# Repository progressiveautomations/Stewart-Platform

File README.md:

# Stewart Platform

## Table of Contents
[Quick Start Guide](#qsg)

[Wiring the Electronics](#wiring)

[Mechanical Assembly](#mech)

[Troubleshooting](#ts)

<a name="qsg"/>

# Quick Start Guide
1. Ensure that power to the platform is turned off, the USB cable from the platform is unplugged from the computer, and all GUI instances are closed.
2. (if Leap Motion is to be used) Ensure that the Leap Motion service and software is started, and the controller is plugged into the computer.
3. Turn on the power to the platform, and plug the USB cable from the platform into the computer.
4. Launch the GUI; in the 'Options' menu, click "Select COM Port".
5. Find the COM port corresponding to the Arduino Due (should show up in the Device Description on the left hand side, as shown), and change the baud rate to 115200.
6. Click connect, and the platform should immediately begin its calibration routine by moving all actuators to full extension, and retracting to minimum position. DO NOT SEND ANY COMMANDS TO THE PLATFORM DURING THIS PHASE!
7. Check the beginning of the log to ensure calibration has succeeded.
8. Manually control the actuators by moving the sliders and/or entering values into the corresponding textbox. To enable Leap Motion, ensure its status is "Connected", and tick the "Enable Leap Motion" checkbox above the sliders.

# Assembly Instructions

<a name="wiring"/>

## Wiring the Electronics

Before assembly, ensure that all the wires are adequately connected within the enclosure, including the power supply wires, the actuator power wires, the actuator signal wires, and the Arduino Due wires. Detail in [how the components are wired together](electronics/electronics_layout.pdf) and individual schematics are located in the `electronics` folder.

To ensure the code under `arduino/platform` is compatible with the wiring of the Arduino Due, the headers on the PCB should be connected to the respective pins in the table below. This assumes actuators 1 through 3 are connected to Multimoto 1 (to blocks M3, M2, and M1 respectively) and actuators 4 through 6 similarly to Multimoto 2. Note the actuator indexing for the PCBs differs from that in software.
- The indexing on the PCBs are ordered by the motor blocks on the Multimoto boards. Indices 1 through 4 correspond to M1 through M4 on Multimoto 1, and the same for indices 5 though 8 with Multimoto 2.
- The indexing in software is ordered by how the signal wires interface with the PCB terminal blocks. This should match the order (left to right) in which they are connected to the enclosure ports.

The UTIL pin headers (RESET, +3.3V, +5V, GND, GND, Vin) are connected to the identically-named Arduino pins and are omitted from this list. The exact pin numbering can be updated in software at `arduino/platform/pin_layout.h` if the wiring configuration needs to be modified.

| Header   | Pin |
|----------|----:|
| POT_1    |  A6 |
| POT_2    |  A7 |
| POT_3    |  A8 |
| POT_4    |  A9 |
| POT_5    | A10 |
| POT_6    | A11 |
| DIR_1    |  41 |
| DIR_2    |  39 |
| DIR_3    |  37 |
| DIR_5    |  35 |
| DIR_6    |  33 |
| DIR_7    |  31 |
| PWM_1    |  13 |
| PWM_2    |  12 |
| PWM_3    |  11 |
| PWM_5    |  10 |
| PWM_6    |   9 |
| PWM_7    |   8 |
| ENABLE_1 |  24 |
| ENABLE_2 |  25 |

<a name="mech"/>

## Mechanical Assembly

Attach the 3 platform legs to the 3 corners of the base plate (Note: the base plate is larger than the top plate, and has 4 slots cut into it.), such that the 6 metal flanges are facing upwards. This is done using the ¾” long, ⅜”-16 threaded bolts, with one washer.

Next, position the enclosure underneath the base, so that the enclosure posts align with the slots in the base plate, with the power and USB connectors facing out as shown.

Attach the enclosure to the base place using 4 1” long,  ¼”-20 threaded bolts, with a washer for each. Ensure the bolts are aligned in the slots such that the corners of the enclosure do not extend beyond the edge of the base plates, like shown.

Attach the actuators as shown in the following picture. Close-up views of the joints are provided. Use 2 washers (one on each side), a lock-washer, and a ¼”-28 nut.

To avoid problems, ensure that the actuator gearboxes are facing upwards as shown in the picture.

Once the platform is assembled, attach the maze to the top plate by aligning the 3 corner holes on each, and secure it with 3 1¼” long, ⅜”-16 threaded bolts, with one washer on each, and a nut.

Connect all the actuator connectors to the appropriate receptacles on the enclosure, by routing the cables around and under the base plate. These can be bundled to be neat and out-of-view.

Finally, connect the power and USB cables to the front of the enclosure, and connect the other end of the USB cable. The platform is now assembled!

<a name="ts"/>

# Troubleshooting

Nothing is moving? Check all power connectors.

Arduino not seen by computer? Check USB cable connection, and ensure the device shows up in Device Manager.

Noisy actuator readings? Adjust the PWM feedback or the filtering capacitances on the Arduino PCB.

## PCB design
The PCBs were designed using [KiCAD v4.0.7](http://kicad.org/).

Each board has its design files under the `electronics` folder, along with Gerber files (under `electronics/gerber`) for the case of reproduction. The individual netlists can be found in the `.sch` files.

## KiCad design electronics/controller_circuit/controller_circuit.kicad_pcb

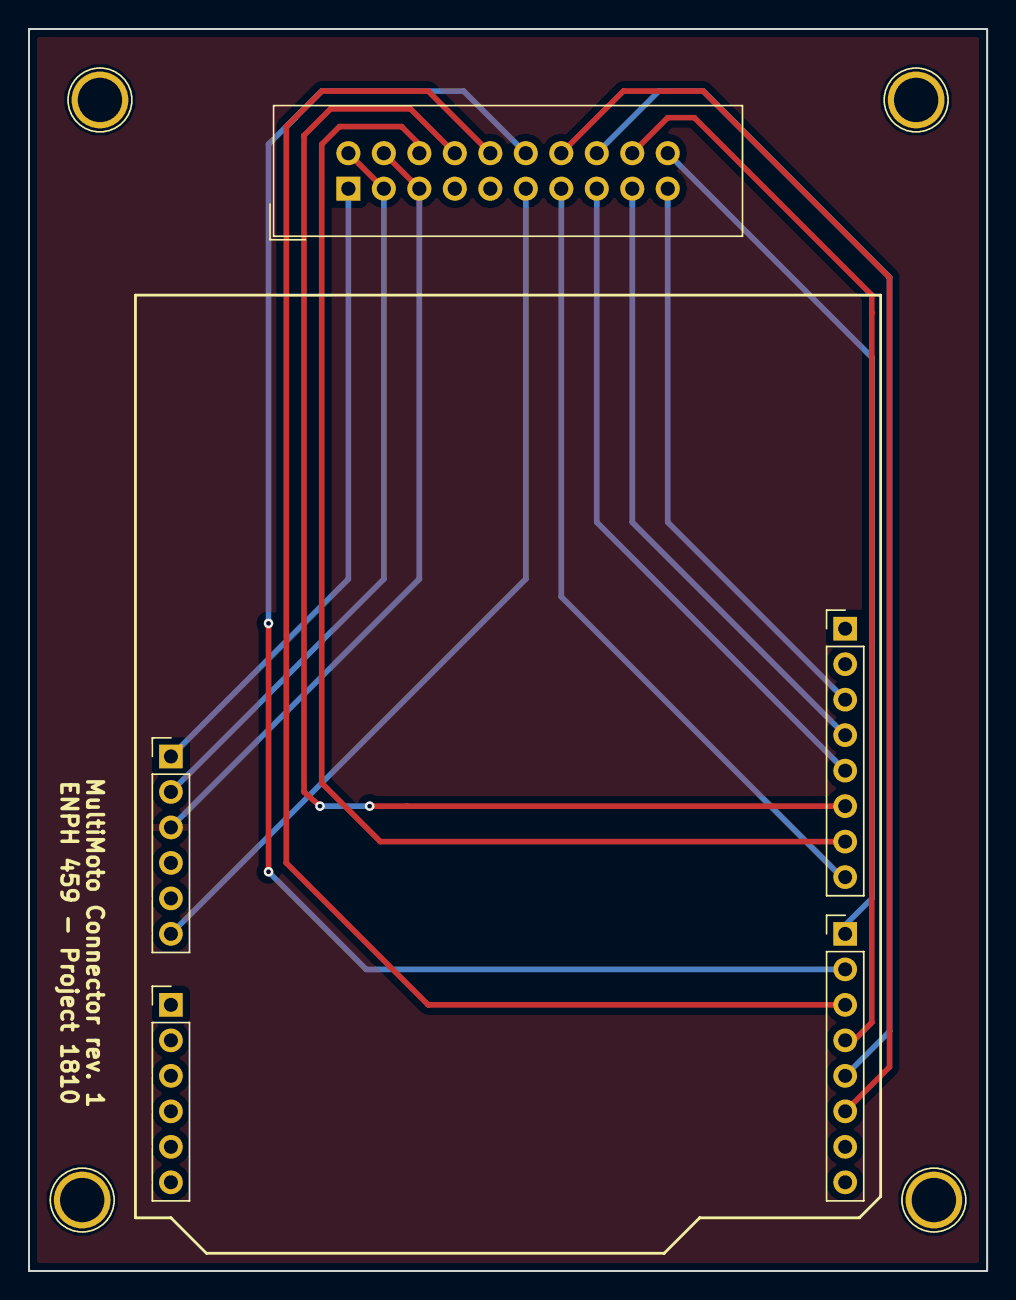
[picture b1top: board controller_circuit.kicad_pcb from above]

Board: 2 copper layers, 68.6 x 88.9 mm, 5 parts (0 on the bottom side), 17 nets.

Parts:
J1: HEADER_10x2; IDC-Header_2x10_Pitch2.54mm_Straight
J2, J3: HEADER_6; Socket_Strip_Straight_1x06_Pitch2.54mm
J4, J5: HEADER_8; Socket_Strip_Straight_1x08_Pitch2.54mm

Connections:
+3.3V: J1.2, J1.3, J2.2
+5V: J1.4, J1.5, J2.3
DIR_1: J1.14, J5.6
DIR_2: J1.16, J5.5
DIR_3: J1.18, J5.4
DIR_4: J1.20, J5.1
GND: J1.7, J1.9, J2.4, J2.5
MISO: J1.17, J4.4
MOSI: J1.15, J4.5
PWM_1: J1.6, J4.7
PWM_2: J1.8, J4.6
PWM_3: J1.10, J5.3
PWM_4: J1.12, J5.2
RESET: J1.1, J2.1
SCLK: J1.19, J4.3
Vin: J1.11, J2.6
~ENABLE~: J1.13, J4.8

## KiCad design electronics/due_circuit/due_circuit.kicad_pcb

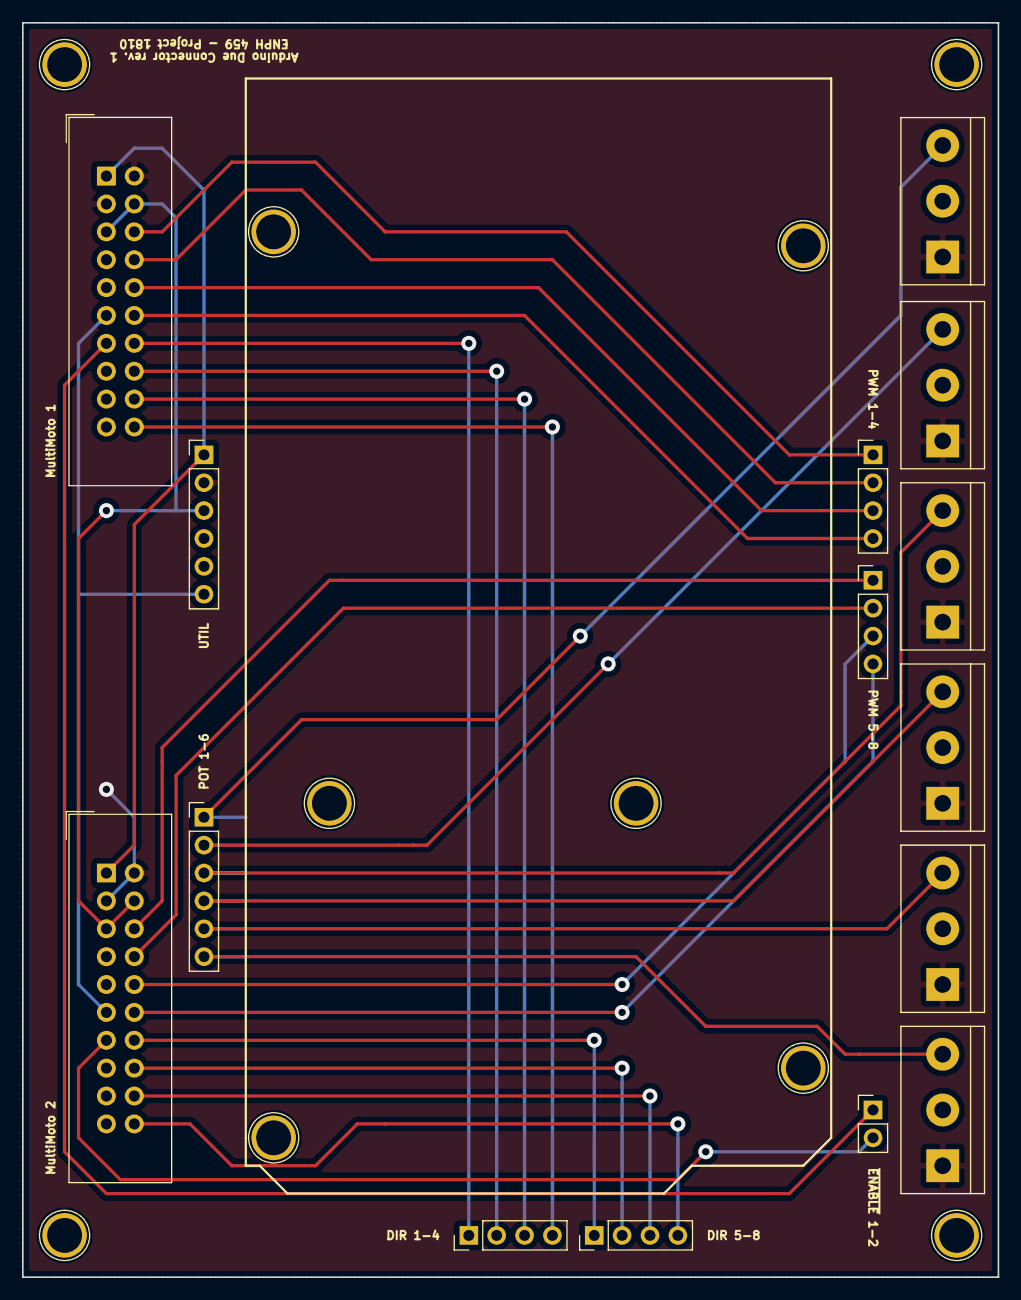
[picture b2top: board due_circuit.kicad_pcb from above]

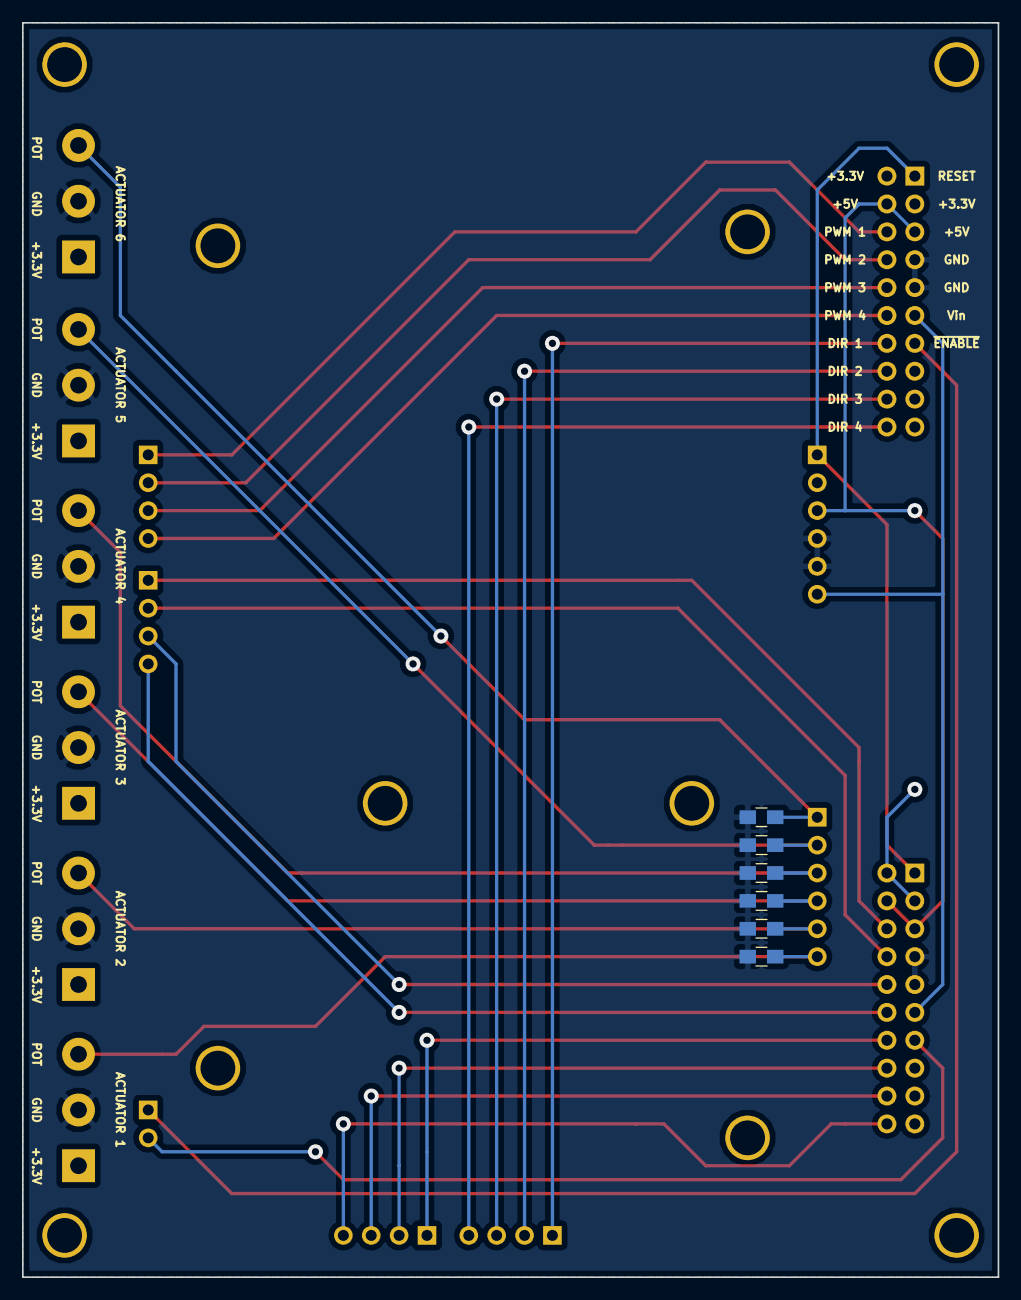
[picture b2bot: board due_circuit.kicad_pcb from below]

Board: 2 copper layers, 88.9 x 114.3 mm, 20 parts (6 on the bottom side), 27 nets.

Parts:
ACTUATOR_1, ACTUATOR_2, ACTUATOR_3, ACTUATOR_4, ACTUATOR_5, ACTUATOR_6: HEADER_3; TerminalBlock_bornier-3_P5.08mm
C1, C2, C3, C4, C5, C6: 10nF; C_0805_HandSoldering
DIR_1-4, DIR_5-8: HEADER_4; Pin_Header_Straight_1x04_Pitch2.54mm
MULTIMOTO_1, MULTIMOTO_2: HEADER_10x2; IDC-Header_2x10_Pitch2.54mm_Straight
POT_OUT_1: HEADER_6; Pin_Header_Straight_1x06_Pitch2.54mm
PWM_1-4, PWM_5-8: HEADER_4; Pin_Header_Straight_1x04_Pitch2.54mm
UTIL_1: HEADER_6; Pin_Header_Straight_1x06_Pitch2.54mm

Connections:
+3.3V: ACTUATOR_1.1, ACTUATOR_2.1, ACTUATOR_3.1, ACTUATOR_4.1, ACTUATOR_5.1, ACTUATOR_6.1, MULTIMOTO_1.2, MULTIMOTO_1.3, MULTIMOTO_2.2, MULTIMOTO_2.3, UTIL_1.2
+5V: MULTIMOTO_1.4, MULTIMOTO_1.5, MULTIMOTO_2.4, MULTIMOTO_2.5, UTIL_1.3
DIR_1: DIR_1-4.1, MULTIMOTO_1.14
DIR_2: DIR_1-4.2, MULTIMOTO_1.16
DIR_3: DIR_1-4.3, MULTIMOTO_1.18
DIR_4: DIR_1-4.4, MULTIMOTO_1.20
DIR_5: DIR_5-8.1, MULTIMOTO_2.14
DIR_6: DIR_5-8.2, MULTIMOTO_2.16
DIR_7: DIR_5-8.3, MULTIMOTO_2.18
DIR_8: DIR_5-8.4, MULTIMOTO_2.20
GND: ACTUATOR_1.2, ACTUATOR_2.2, ACTUATOR_3.2, ACTUATOR_4.2, ACTUATOR_5.2, ACTUATOR_6.2, C1.2, C2.2, C3.2, C4.2, C5.2, C6.2, MULTIMOTO_1.7, MULTIMOTO_1.9, MULTIMOTO_2.7, MULTIMOTO_2.9, UTIL_1.4, UTIL_1.5
POT_1: ACTUATOR_1.3, C1.1, POT_OUT_1.6
POT_2: ACTUATOR_2.3, C2.1, POT_OUT_1.5
POT_3: ACTUATOR_3.3, C3.1, POT_OUT_1.4
POT_4: ACTUATOR_4.3, C4.1, POT_OUT_1.3
POT_5: ACTUATOR_5.3, C5.1, POT_OUT_1.2
POT_6: ACTUATOR_6.3, C6.1, POT_OUT_1.1
PWM_1: MULTIMOTO_1.6, PWM_1-4.1
PWM_2: MULTIMOTO_1.8, PWM_1-4.2
PWM_3: MULTIMOTO_1.10, PWM_1-4.3
PWM_4: MULTIMOTO_1.12, PWM_1-4.4
PWM_5: MULTIMOTO_2.6, PWM_5-8.1
PWM_6: MULTIMOTO_2.8, PWM_5-8.2
PWM_7: MULTIMOTO_2.10, PWM_5-8.3
PWM_8: MULTIMOTO_2.12, PWM_5-8.4
RESET: MULTIMOTO_1.1, MULTIMOTO_2.1, UTIL_1.1
Vin: MULTIMOTO_1.11, MULTIMOTO_2.11, UTIL_1.6

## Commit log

2017-10-25 Add .gitignore and .gitattributes.
2017-10-25 Add project files.
2017-10-25 Create initial README
2017-10-28 Changed direction to enum from bool
2017-10-29 Fixed serial input parsing
2017-11-05 Recalibrated actuators, fixed mapping of motor position values
2017-11-11 Add initial changes/dependencies
2017-11-11 Major code refactor; archive serial code for feature redesign
2017-11-11 Rename header file
2017-11-11 Add basic thread framework
2017-11-12 Used parseInt() for serial parsing
2017-11-12 Initial addition of Leap Motion python
2017-11-12 Ported Leap Motion code to Python, untested!!!
2017-11-12 Got serial input working through threads (without actuator code)
2017-11-12 Integrate actuator code with thread code
2017-11-12 Minor refactoring
2017-11-12 More refactoring, less hardcoding
2017-11-12 Fixed some bugs, should be somewhat working now (not tested with serial yet)
2017-11-12 Rename thread functions for consistency
2017-11-12 Update README with Leap Motion changes
2017-11-12 Fix indentation and spacing
2017-11-12 Move printing to improve thread spec; weakened pattern matching a bit
2017-11-12 Added more comments to LeapMotion python file
2017-11-13 Fix logic bug that could potentially cause buffer issues
2017-11-13 Minor changes
2017-11-14 Try PWM scaling
2017-11-14 Ignore compiled Arduino hex from Sublime
2017-11-25 Initial implementation of 12-byte stream sending and receiving, untested
2017-11-25 Removed __vm from source control, updated .gitignore
2017-11-25 Commit updated .gitignore
2017-11-25 Merged LeapMotionControl.py
2017-11-26 Byte parsing seems to be working (freezes after about a minute)
2017-11-26 Modify input reading to normalize from a larger set; adjust PWM and direction setting; add Leap Motion (3.2.1+45911) files
2017-11-26 Slight refactor of Leap Motion code; getting errors with serial object
2017-11-26 Add timeout and flow control options for Leap Motion
2017-11-26 Remove extraneous/project files
2017-11-26 Additional formatting changes and refactor
2017-11-27 Decrease baud rate, add watchdog timer, increase frame rate
2017-11-27 Temporarily disable additional debug statements (not useful while running with Leap Motion)
2017-12-07 Comment out watchdog timer
2017-12-10 Further adjustment of values
2017-12-10 Fixed exception handling for Leap Motion to transfer indefinitely
2017-12-10 Remove SPI configuration; disable serial printing; re-enable Leap Motion frame rate
2017-12-11 removed pythoncontrol folder
2018-01-04 Adjust PWM feedback; a lot smoother now
2018-01-04 Ported code in master branch to Arduino Due
2018-01-05 Initial commit of input_threading port to Due
2018-01-05 updated pwm and desired_pos arrays to int16_t for compilation
2018-01-05 Recalibrated position and PWM values for the Due, still need to complete implementation for motor movement direction
2018-01-06 Major refactoring; completed movement order/priority of actuators
2018-01-06 Add better formatting/documentation
2018-01-12 Revert movement order code, @todo: modify pin layout
2018-01-12 Updated pins to new circuit board layout
2018-01-17 Refactoring, platform is very responsive now; test changes for MacOS Leap Motion
2018-01-26 Add initial GUI files
2018-01-28 Separate Leap Motion files into Windows/Mac due to dependency issues on Windows
2018-01-28 Add serial/timeout changes from threading branch to the Leap Motion Python script
2018-01-30 Changed serial/line-endings to fix issues on Windows
2018-02-06 Rename GUI elements, got include dependencies and exit button working
2018-02-06 Add LeapEventListener files; ignore build files (for now)
2018-02-07 Add in-progress serial port code
2018-02-16 Use QSerialPort and QMatrix instead of Boost and Windows API
2018-02-16 Added LGPL License for Qt
2018-02-21 Serial port selection and logging is working
2018-02-21 -Changed QLineEdit to QSpinBox, platform can now send values to platform -Added Leap Motion checkbox, disables manual control if checked
2018-02-21 Fixes for Leap Motion compilation
2018-02-21 Ported Leap Motion code, untested; need to figure out how to link with StewartPlatform class
2018-02-21 Integrated Leap Motion, untested
2018-02-21 Leap library now statically linked into executable
2018-02-21 Minor cleanup
2018-02-22 Register QVector in GUI for Leap Motion error
2018-02-22 Add refactored Arduino files (clean up code, update calibration values)
2018-02-22 Add early PID code; yet to be tested and tuned
2018-02-22 Clean up files in master branch
2018-02-22 Minor formatting changes
2018-02-22 Refactored Python Leap Motion control
2018-02-25 Updated Leap.py for Mac
2018-02-25 Added MacOS Leap library to .pro
2018-02-26 Fix bug in serial int parsing
2018-03-02 Formatting changes
2018-03-02 Modified logging, modified Leap Motion transform matrix
2018-03-04 Refactor Arduino code for PID control, add performance script to measure positional accuracy
2018-03-13 Switch fields/sliders to separate vectors to fix actuator mismatch from QMap ordering
2018-03-16 Added calibration to startup routine
2018-03-28 Clean up and improve logging for Arduino code
2018-03-29 Update calibration and PID tuning
2018-03-29 Test explicit matrix multiplication for Leap Motion in GUI
2018-03-29 Fixed misusing arcsin/cos functions
2018-03-30 Remove old Arduino files, wait for serial connection before setup/calibration
2018-03-30 Rename Python folder, create separate scripts folder
2018-03-30 Use QStringBuilder for concatenation, extra clean-up of GUI code
2018-03-30 Add design, schematic, and gerber files for electronics/PCBs
2018-03-31 Add in-progress logging improvements
2018-03-31 Adjust platform height and actuator lengths to physical dimensions, remove Help menu as it is currently unused
2018-03-31 Adjust PID based on script results
2018-04-04 Create Mechanical
    I don't know how to make a folder otherwise
2018-04-04 Create Folder
    Folder
2018-04-04 Added solidworks files, DXF files, mechanical drawing files and drawing pdfs.
2018-04-04 Update with initial version of Quick Start guide.
2018-04-06 Added standalone GUI zip
2018-04-06 Added assembly instructions
2018-04-06 Added images
2018-04-06 Removed weird file from images
2018-04-07 Modify mechanical folder to align with directory naming
2018-04-07 Temporarily remove mechanical folder for renaming
2018-04-07 Re-add mechanical files from last commit with correct directory
2018-04-07 Add wiring instructions to README.md
2018-04-08 Added Mech pictures to README
2018-04-13 renamed some images
2018-04-14 Add PCB design section to wiki
2018-05-03 Update README with wiring pics, ToC
2018-05-03 Fixed ToC references
2018-05-03 More ToC formatting changes
2021-11-10 Update README.md
    https://forum.kicad.info/t/warning-avoid-all-links-to-kicad-pcb-org-use-kicad-org/31521
